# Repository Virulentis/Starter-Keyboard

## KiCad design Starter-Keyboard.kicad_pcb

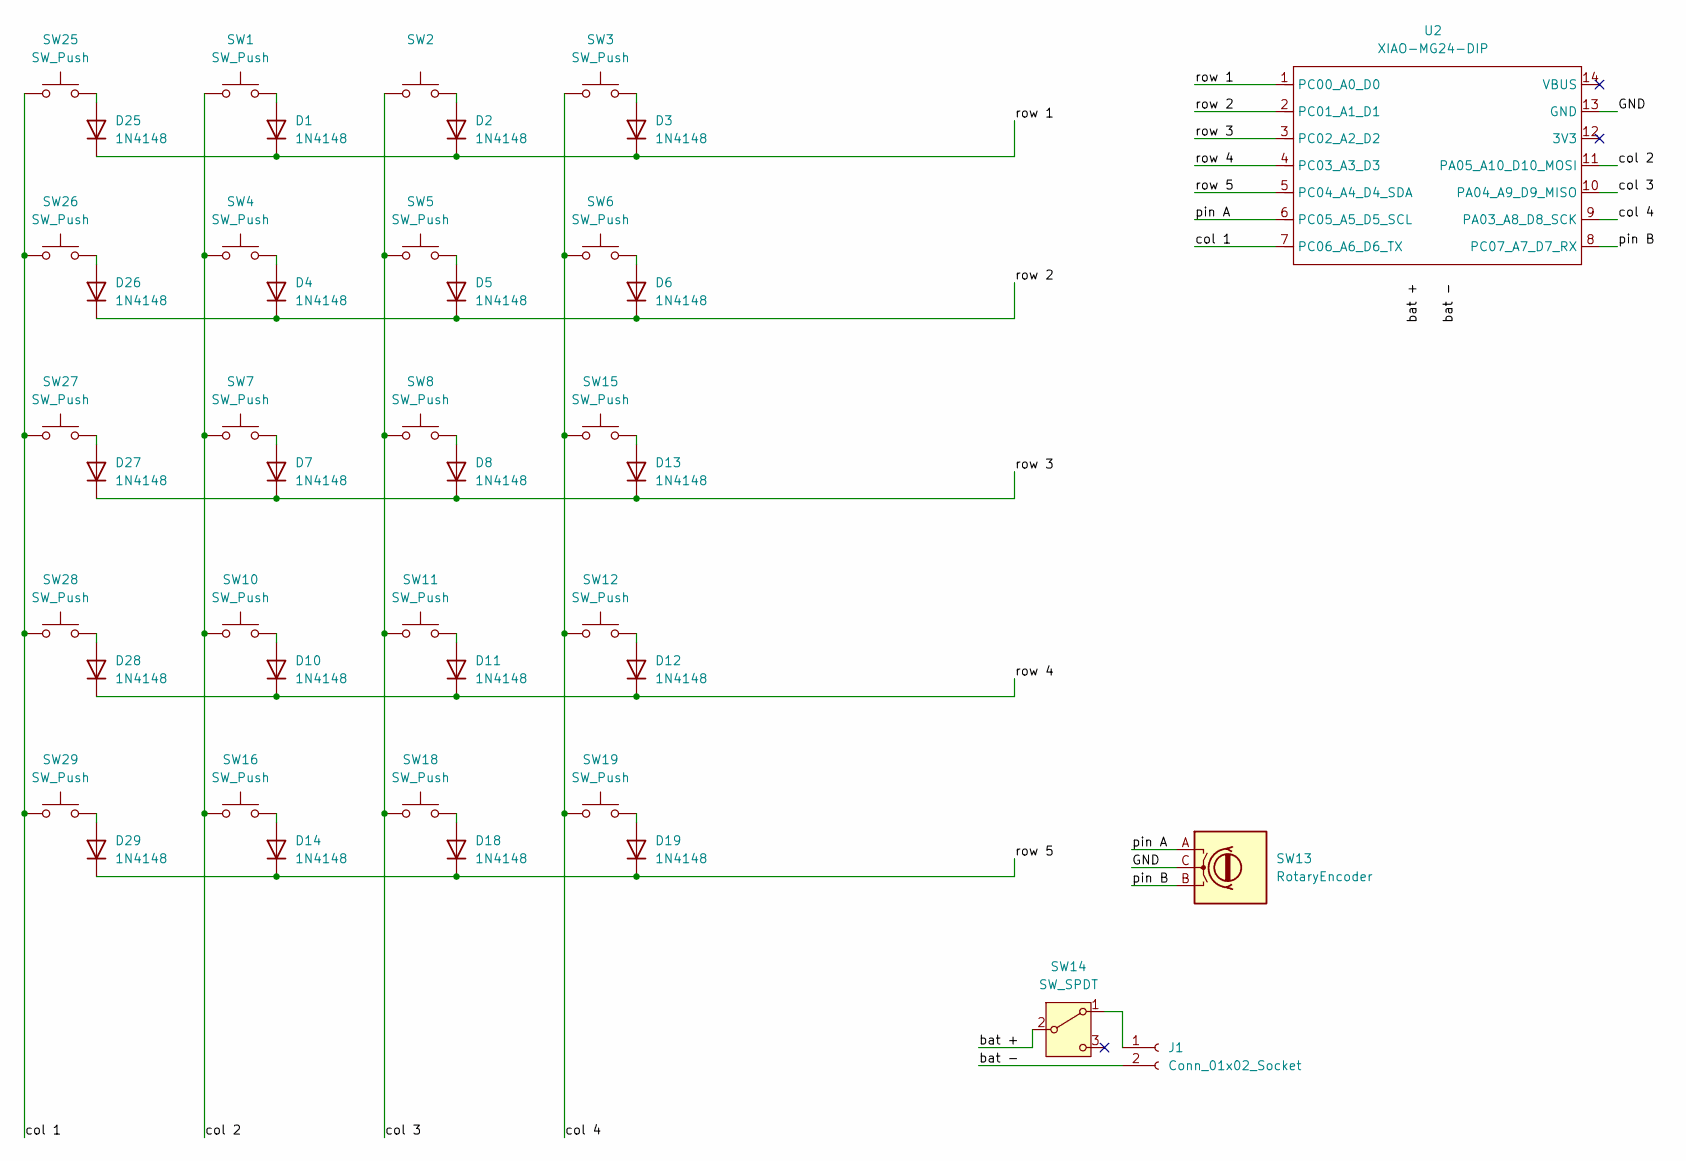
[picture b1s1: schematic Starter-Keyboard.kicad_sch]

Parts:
D1, D2, D3, D4, D5, D6, D7, D8, D10, D11, D12, D13, D14, D18, D19, D25, D26, D27, D28, D29: 1N4148; D_DO-35_SOD27_P7.62mm_Horizontal
J1: Conn_01x02_Socket; JST_PH_S2B-PH-SM4-TB_1x02-1MP_P2.00mm_Horizontal
SW1, SW2, SW3, SW4, SW5, SW6, SW7, SW8, SW10, SW11, SW12, SW15, SW16, SW18, SW19, SW25, SW26, SW27, SW28, SW29: SW_Push; Gateron-KS33-Hotswap-1U
SW13: RotaryEncoder; XDCR_PEC11R-4220F-S0024
SW14: SW_SPDT; SW_SPDT_PCM12
U2: XIAO-MG24-DIP

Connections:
/GND: SW13.C, U2.13 (GND); also elsewhere on the board
/bat +: SW14.2 (B); also elsewhere on the board
/bat -: J1.2; also elsewhere on the board
/col 1: SW25.1, SW26.1, SW27.1, SW28.1, SW29.1, U2.7 (PC06_A6_D6_TX); also elsewhere on the board
/col 2: SW1.1, SW4.1, SW7.1, SW10.1, SW16.1, U2.11 (PA05_A10_D10_MOSI); also elsewhere on the board
/col 3: SW2.1, SW5.1, SW8.1, SW11.1, SW18.1, U2.10 (PA04_A9_D9_MISO); also elsewhere on the board
/col 4: SW3.1, SW6.1, SW12.1, SW15.1, SW19.1, U2.9 (PA03_A8_D8_SCK); also elsewhere on the board
/pin A: SW13.A, U2.6 (PC05_A5_D5_SCL); also elsewhere on the board
/pin B: SW13.B, U2.8 (PC07_A7_D7_RX); also elsewhere on the board
/row 1: D1.1 (K), D2.1 (K), D3.1 (K), D25.1 (K), U2.1 (PC00_A0_D0); also elsewhere on the board
/row 2: D4.1 (K), D5.1 (K), D6.1 (K), D26.1 (K), U2.2 (PC01_A1_D1); also elsewhere on the board
/row 3: D7.1 (K), D8.1 (K), D13.1 (K), D27.1 (K), U2.3 (PC02_A2_D2); also elsewhere on the board
/row 4: D10.1 (K), D11.1 (K), D12.1 (K), D28.1 (K), U2.4 (PC03_A3_D3); also elsewhere on the board
/row 5: D14.1 (K), D18.1 (K), D19.1 (K), D29.1 (K), U2.5 (PC04_A4_D4_SDA); also elsewhere on the board
unnamed: D1.2 (A), SW1.2
unnamed: D2.2 (A), SW2.2
unnamed: D3.2 (A), SW3.2
unnamed: D4.2 (A), SW4.2
unnamed: D5.2 (A), SW5.2
unnamed: D6.2 (A), SW6.2
unnamed: D7.2 (A), SW7.2
unnamed: D8.2 (A), SW8.2
unnamed: D10.2 (A), SW10.2
unnamed: D11.2 (A), SW11.2
unnamed: D12.2 (A), SW12.2
unnamed: D13.2 (A), SW15.2
unnamed: D14.2 (A), SW16.2
unnamed: D18.2 (A), SW18.2
unnamed: D19.2 (A), SW19.2
unnamed: D25.2 (A), SW25.2
unnamed: D26.2 (A), SW26.2
unnamed: D27.2 (A), SW27.2
unnamed: D28.2 (A), SW28.2
unnamed: D29.2 (A), SW29.2
unnamed: J1.1, SW14.1 (A)

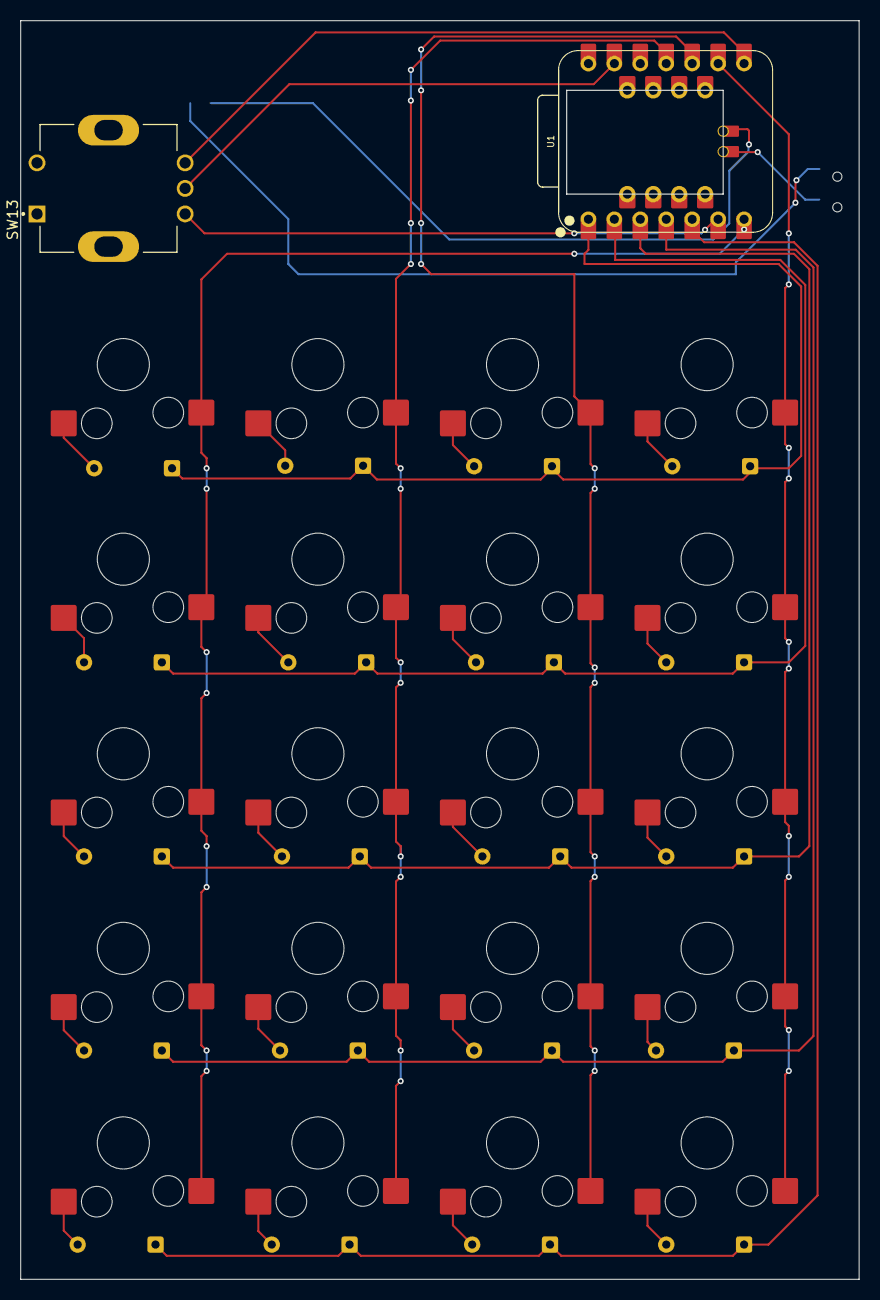
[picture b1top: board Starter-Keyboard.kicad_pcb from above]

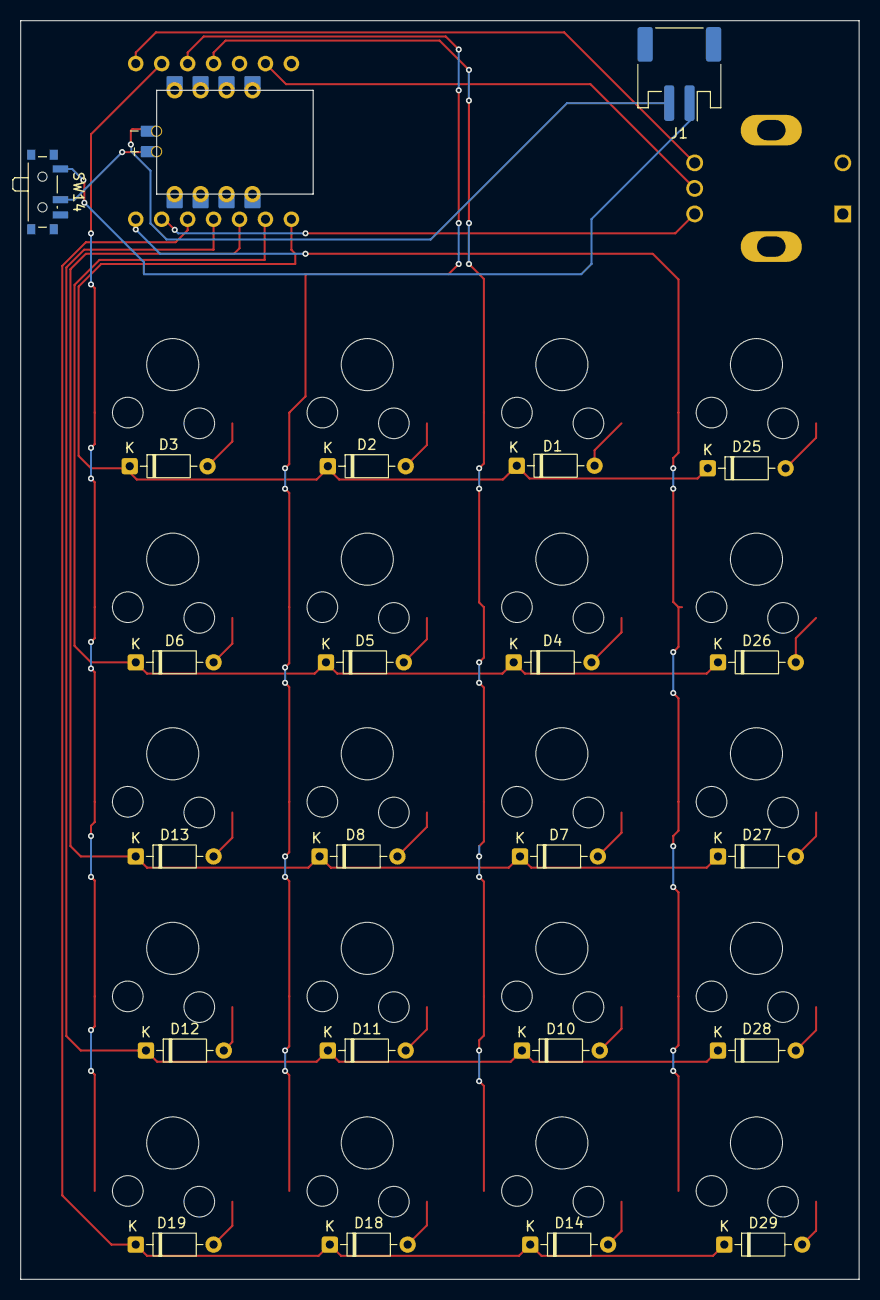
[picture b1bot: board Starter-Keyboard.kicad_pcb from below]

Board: 2 copper layers, 82.0 x 123.1 mm, 44 parts (22 on the bottom side), 35 nets.

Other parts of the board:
U1: XIAO-MG24-DIP

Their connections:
/GND: U1.13 (GND); also elsewhere on the board
/bat +: U1.31; also elsewhere on the board
/bat -: U1.32; also elsewhere on the board
/col 1: U1.7 (PC06_A6_D6_TX); also elsewhere on the board
/col 2: U1.11 (PA05_A10_D10_MOSI); also elsewhere on the board
/col 3: U1.10 (PA04_A9_D9_MISO); also elsewhere on the board
/col 4: U1.9 (PA03_A8_D8_SCK); also elsewhere on the board
/pin A: U1.6 (PC05_A5_D5_SCL); also elsewhere on the board
/pin B: U1.8 (PC07_A7_D7_RX); also elsewhere on the board
/row 1: U1.1 (PC00_A0_D0); also elsewhere on the board
/row 2: U1.2 (PC01_A1_D1); also elsewhere on the board
/row 3: U1.3 (PC02_A2_D2); also elsewhere on the board
/row 4: U1.4 (PC03_A3_D3); also elsewhere on the board
/row 5: U1.5 (PC04_A4_D4_SDA); also elsewhere on the board

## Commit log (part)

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2026-04-28 Add submodules
2026-05-01 updated keyboard, started work on pcb
